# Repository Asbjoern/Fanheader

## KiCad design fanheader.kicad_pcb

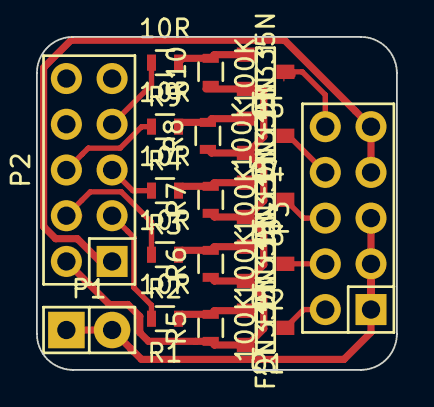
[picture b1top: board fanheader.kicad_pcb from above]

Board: 2 copper layers, 20.0 x 18.5 mm, 18 parts (0 on the bottom side), 18 nets.

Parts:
P1: 12V; Pin_Header_Straight_1x02
P2: AUX-2; Pin_Header_Straight_2x05
P3: CONN_01X10; Pin_Header_Straight_2x05
Q1, Q2, Q3, Q4, Q5: FDN335N; SOT-23
R1, R2, R3, R4, R9: 10R; R_0603
R5, R6, R7, R8, R10: 100K; R_0603

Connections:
+12V: P1.1, P1.2, P3.1, P3.3, P3.5
/A5: P2.3, R1.2
/A9: P2.4, R2.2
/A10: P2.5, R3.2
/D40: P2.6, R4.2
/D44: P2.7, R9.2
GND: P2.2, Q1.2, Q2.2, Q3.2, Q4.2, Q5.2, R5.1, R6.1, R7.1, R8.1, R10.1
unnamed: P3.2, Q1.3
unnamed: P3.4, Q2.3
unnamed: P3.6, Q3.3
unnamed: P3.8, Q4.3
unnamed: P3.10, Q5.3
unnamed: Q1.1, R1.1, R5.2
unnamed: Q2.1, R2.1, R6.2
unnamed: Q3.1, R3.1, R7.2
unnamed: Q4.1, R4.1, R8.2
unnamed: Q5.1, R9.1, R10.2
VCC: P2.1, P3.7, P3.9

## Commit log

2015-05-08 Fan connection to RAMPS 1.4 module
2016-02-23 New KiCad
